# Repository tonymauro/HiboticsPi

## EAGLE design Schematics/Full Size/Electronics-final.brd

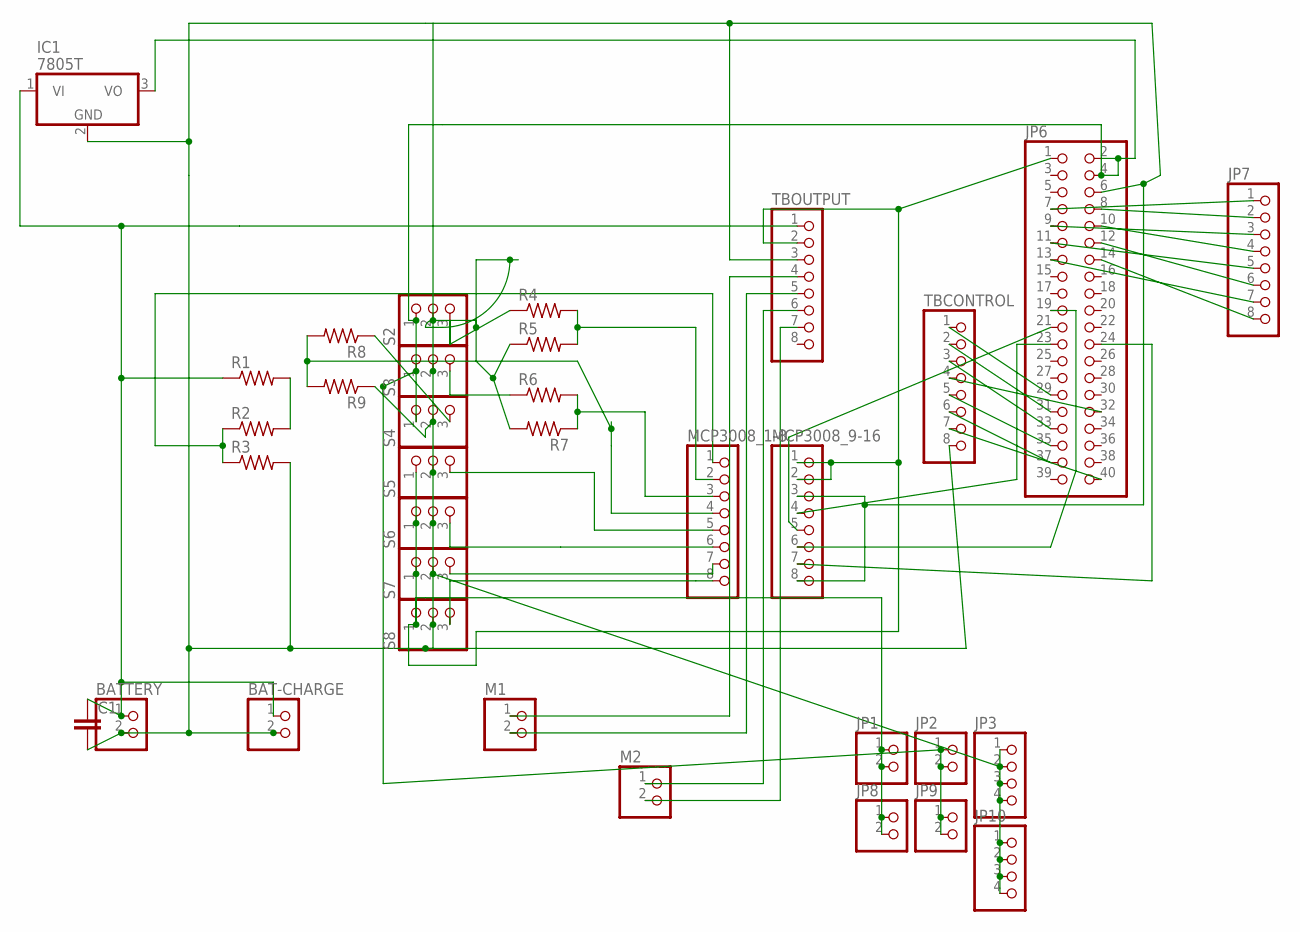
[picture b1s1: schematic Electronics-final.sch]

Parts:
BAT-CHARGE: PINHD-1X2; 1X02
BATTERY: PINHD-1X2; 1X02
C1: C-EU050-035X075; C050-035X075
IC1: 7805T; TO220H
JP1, JP2, JP8, JP9: PINHD-1X2; 1X02
JP3, JP10: PINHD-1X4; 1X04
JP6: PINHD-2X20; 2X20
JP7: PINHD-1X8; 1X08
M1, M2: PINHD-1X2; 1X02
MCP3008_1-8, MCP3008_9-16: PINHD-1X8; 1X08
R1, R2, R3, R4, R5, R6, R7, R8, R9: R-US_0204/7; 0204/7
S2, S3, S4, S5, S6, S7, S8: PINHD-1X3; 1X03
TBCONTROL: PINHD-1X8; 1X08
TBOUTPUT: PINHD-1X8; 1X08

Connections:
3.3V: JP1.1, JP1.2, JP6.1, JP8.1, JP8.2, MCP3008_9-16.1, MCP3008_9-16.2, S5.1, S6.1, S7.1, S8.1, TBOUTPUT.2
5V: IC1.3 (VO), JP2.1, JP2.2, JP6.2, JP6.4, JP9.1, JP9.2, S2.1, S3.1, S4.1
7: JP6.7, JP7.1
8: JP6.8, JP7.2
9: JP6.9, JP7.3
10: JP6.10, JP7.4
11: JP6.11, JP7.5
12: JP6.12, JP7.6
13: JP6.13, JP7.7
14: JP6.14, JP7.8
GND: BAT-CHARGE.2, BATTERY.2, C1.2, IC1.2 (GND), JP3.1, JP3.2, JP3.3, JP3.4, JP6.6, JP10.1, JP10.2, JP10.3, JP10.4, MCP3008_9-16.3, MCP3008_9-16.8, R3.2, R5.1, R7.2, R9.1, S2.2, S3.2, S4.2, S5.2, S6.2, S7.2, S8.2, TBCONTROL.8, TBOUTPUT.3
unnamed: JP6.40, TBCONTROL.7
unnamed: JP6.32, TBCONTROL.4
unnamed: R1.2, R2.2
unnamed: JP6.37, TBCONTROL.6
unnamed: JP6.35, TBCONTROL.5
unnamed: JP6.33, TBCONTROL.3
unnamed: JP6.31, TBCONTROL.2
unnamed: JP6.29, TBCONTROL.1
unnamed: JP6.23, MCP3008_9-16.4
unnamed: JP6.21, MCP3008_9-16.5
unnamed: M1.1, TBOUTPUT.4
unnamed: M1.2, TBOUTPUT.5
unnamed: M2.1, TBOUTPUT.6
unnamed: M2.2, TBOUTPUT.7
unnamed: JP6.19, MCP3008_9-16.6
unnamed: JP6.24, MCP3008_9-16.7
S1: R4.1, S2.3
S1H: MCP3008_1-8.2, R4.2, R5.2
S2: R6.1, S3.3
S2H: MCP3008_1-8.3, R6.2, R7.1
S3: R8.1, S4.3
S3H: MCP3008_1-8.4, R8.2, R9.2
S4: MCP3008_1-8.5, S5.3
S5: MCP3008_1-8.6, S6.3
S6: MCP3008_1-8.7, S7.3
S7: MCP3008_1-8.8, S8.3
VIN: BAT-CHARGE.1, BATTERY.1, C1.1, IC1.1 (VI), R1.1, TBOUTPUT.1
VINH: MCP3008_1-8.1, R2.1, R3.1

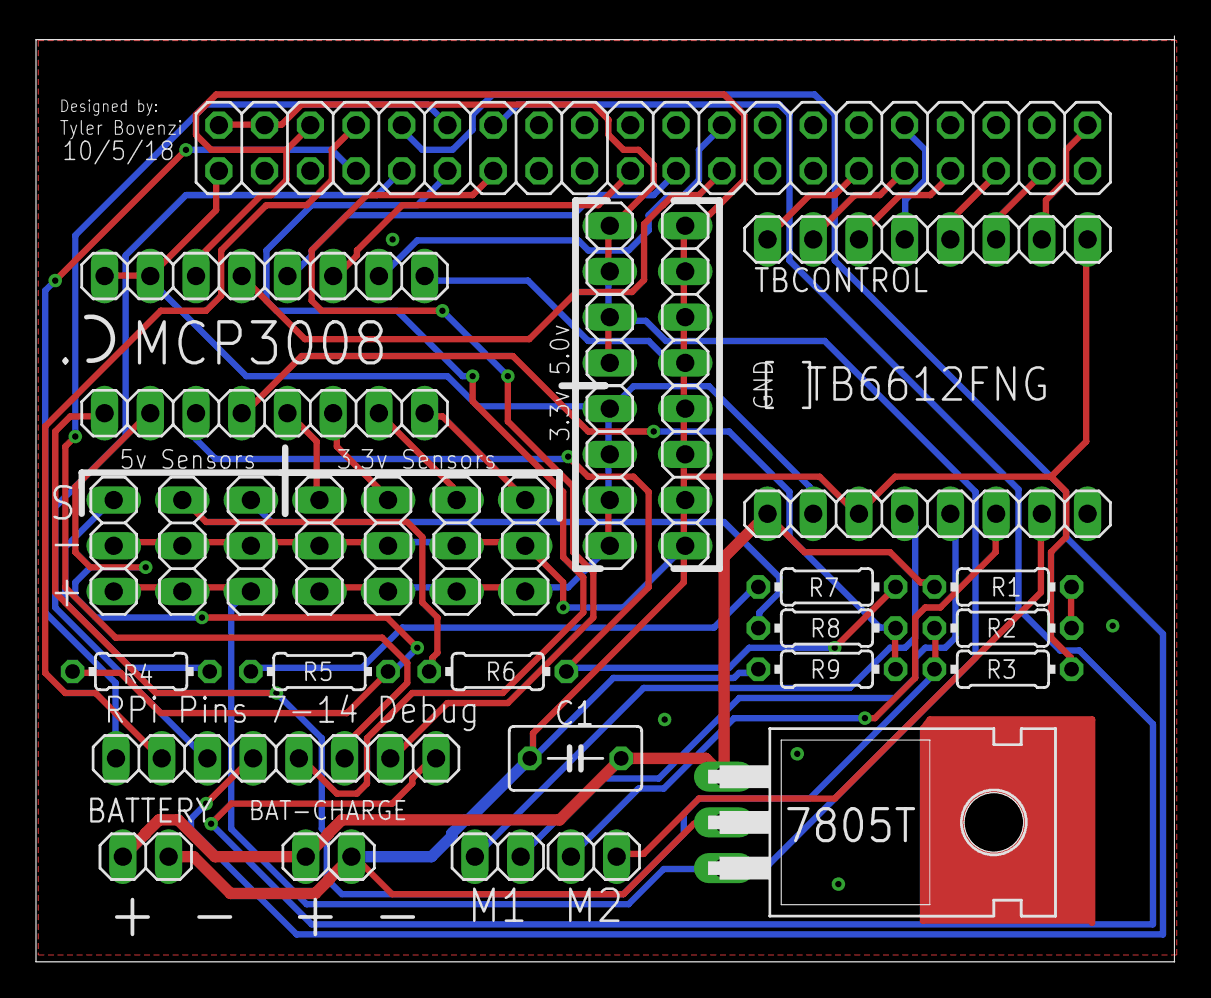
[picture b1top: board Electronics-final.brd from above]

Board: 2 copper layers, 63.3 x 51.4 mm, 34 parts (0 on the bottom side), 39 nets.

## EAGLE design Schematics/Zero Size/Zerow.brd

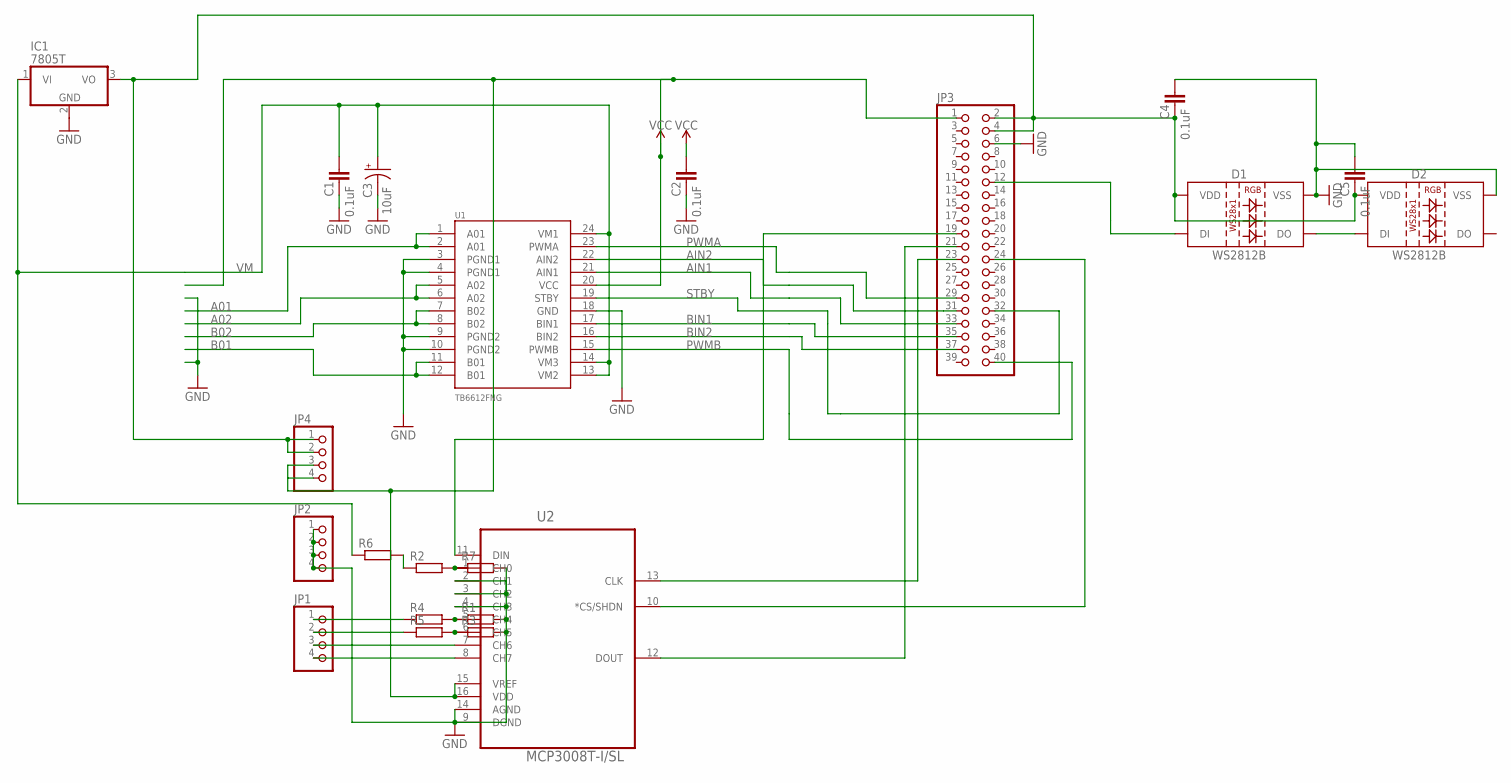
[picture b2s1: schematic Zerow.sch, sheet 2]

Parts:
C1, C2, C4, C5: 0.1uF; 0402
C3: 10uF; EIA3528
D1, D2: WS2812B
IC1: 7805T; TO220H
JP1, JP2, JP4: PINHD-1X4; 1X04
JP3: PINHD-2X20; 2X20
R1, R2, R3, R4, R5, R6, R7: R-EU_R0805; R0805
U1: TB6612FNG; SSOP24
U2: MCP3008T-I/SL; SOIC127P600X175-16N

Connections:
5V: C4.2, C5.2, D1.1 (VDD), D2.1 (VDD), IC1.3 (VO), JP3.2, JP3.4, JP4.1, JP4.2
A01: U1.1 (A01), U1.2 (A01)
A02: U1.5 (A02), U1.6 (A02)
AIN1: JP3.33, U1.21 (AIN1)
AIN2: JP3.31, U1.22 (AIN2)
B01: U1.11 (B01), U1.12 (B01)
B02: U1.7 (B02), U1.8 (B02)
BIN1: JP3.35, U1.17 (BIN1)
BIN2: JP3.37, U1.16 (BIN2)
GND: C1.2, C2.2, C3.C (-), C4.1, C5.1, D1.3 (VSS), D2.3 (VSS), IC1.2 (GND), JP2.1, JP2.2, JP2.3, JP2.4, JP3.6, R1.2, R3.2, R7.2, U1.3 (PGND1), U1.4 (PGND1), U1.9 (PGND2), U1.10 (PGND2), U1.18 (GND), U2.2 (CH1), U2.3 (CH2), U2.4 (CH3), U2.9 (DGND), U2.14 (AGND)
unnamed: JP3.23, U2.13 (CLK)
unnamed: JP3.19, U2.11 (DIN)
unnamed: JP3.21, U2.12 (DOUT)
unnamed: JP3.24, U2.10 (*CS/SHDN)
unnamed: JP1.4, U2.8 (CH7)
unnamed: JP1.3, U2.7 (CH6)
unnamed: R1.1, R4.2, U2.5 (CH4)
unnamed: R3.1, R5.2, U2.6 (CH5)
unnamed: JP1.1, R4.1
unnamed: JP1.2, R5.1
unnamed: R2.2, R7.1, U2.1 (CH0)
unnamed: R2.1, R6.2
unnamed: D1.4 (DI), JP3.12
unnamed: D1.2 (DO), D2.4 (DI)
PWMA: JP3.29, U1.23 (PWMA)
PWMB: JP3.40, U1.15 (PWMB)
STBY: JP3.32, U1.19 (STBY)
VCC: C2.1, JP3.1, JP4.3, JP4.4, U1.20 (VCC), U2.15 (VREF), U2.16 (VDD)
VM: C1.1, C3.A (+), IC1.1 (VI), R6.1, U1.13 (VM2), U1.14 (VM3), U1.24 (VM1)

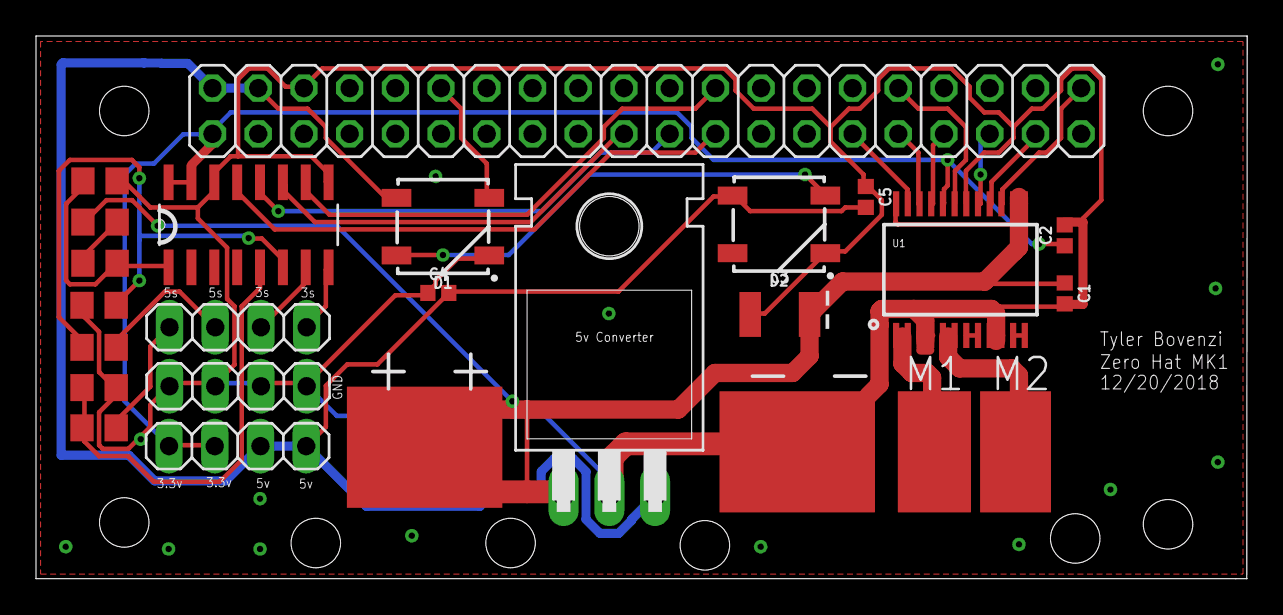
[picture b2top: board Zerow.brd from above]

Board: 2 copper layers, 67.3 x 30.1 mm, 21 parts (0 on the bottom side), 29 nets.

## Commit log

2019-06-18 Added Tyler B's original development
2019-06-18 Added documentation
2019-06-20 Refactoring & reformatting
    Not needed, but good practice nevertheless

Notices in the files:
parts and their libraries:
SparkFun-IC-Special-Function: Licensing: Creative Commons ShareAlike 4.0 International - https://creativecommons.org/licenses/by-sa/4.0
